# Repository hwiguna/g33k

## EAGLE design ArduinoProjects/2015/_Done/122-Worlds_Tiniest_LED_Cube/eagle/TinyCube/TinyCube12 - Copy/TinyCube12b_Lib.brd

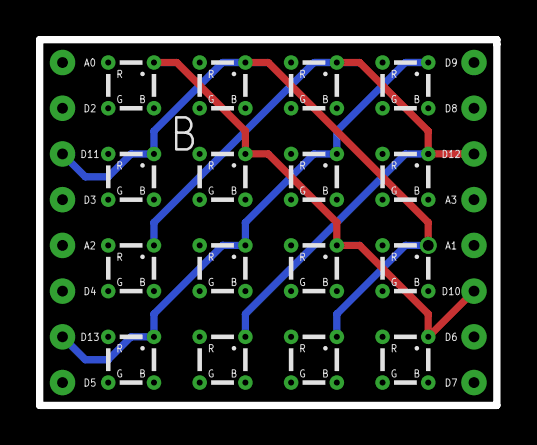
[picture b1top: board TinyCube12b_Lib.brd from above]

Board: 2 copper layers, 25.4 x 20.3 mm, 18 parts (0 on the bottom side), 4 nets.

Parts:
U$1, U$2, U$3, U$4, U$5, U$6, U$7, U$8, U$9, U$10, U$11, U$12, U$13, U$14, U$15, U$16: PILLAR; 10MIL
U$17, U$18: TINY_HEADER_DEV; TINY_HEADER_PKG

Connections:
unnamed: U$2.+, U$5.+, U$12.+, U$15.+, U$17.P$3
unnamed: U$4.+, U$7.+, U$10.+, U$13.+, U$17.P$7
unnamed: U$1.+, U$6.+, U$11.+, U$16.+, U$18.P$6
unnamed: U$3.+, U$8.+, U$9.+, U$14.+, U$18.P$3
